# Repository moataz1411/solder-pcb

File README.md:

# solder-pcb

A simple custom shaped PCB designed as a shark keychain with leds.

The goal of the project was to combine electronic circuit with a creative PCB shape to make a cool keychain.

---

## Bill of Materials

| Component | Value | Qty |
|-----------|-------|-----|
| CR2032 Battery Holder | 3V | 1 |
| 5mm LED | Red | 3 |
| Resistor | 470Ω | 3 |
| Push Button | 6mm | 1 |

**Total: 8 components**

---

schematic photo

---

pcb photo

---

3d view

--- 

#my user  : mezoahmed1411

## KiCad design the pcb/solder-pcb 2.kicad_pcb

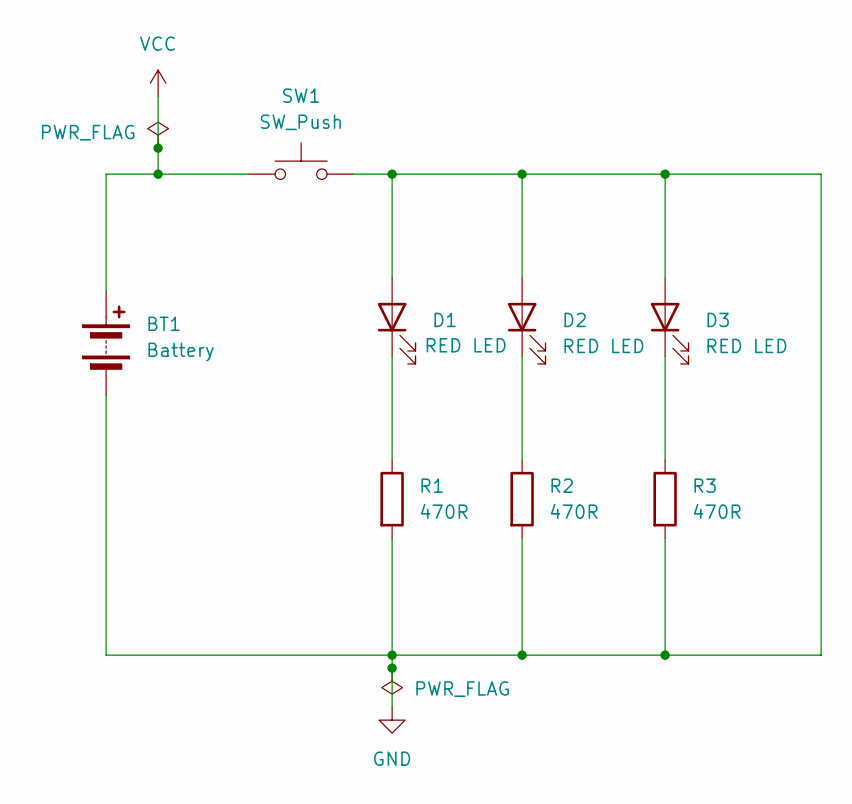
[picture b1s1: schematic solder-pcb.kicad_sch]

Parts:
BT1: Battery; Texas_DRC0010J_ThermalVias
D1, D2, D3: RED LED
R1, R2, R3: 470R
SW1: SW_Push; DIP-24_W7.62mm

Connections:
GND: BT1.2 (-), D1.2 (A), D2.2 (A), D3.2 (A), R1.2, R2.2, R3.2, SW1.2
unnamed: D1.1 (K), R1.1
unnamed: D2.1 (K), R2.1
unnamed: D3.1 (K), R3.1
VCC: BT1.1 (+), SW1.1

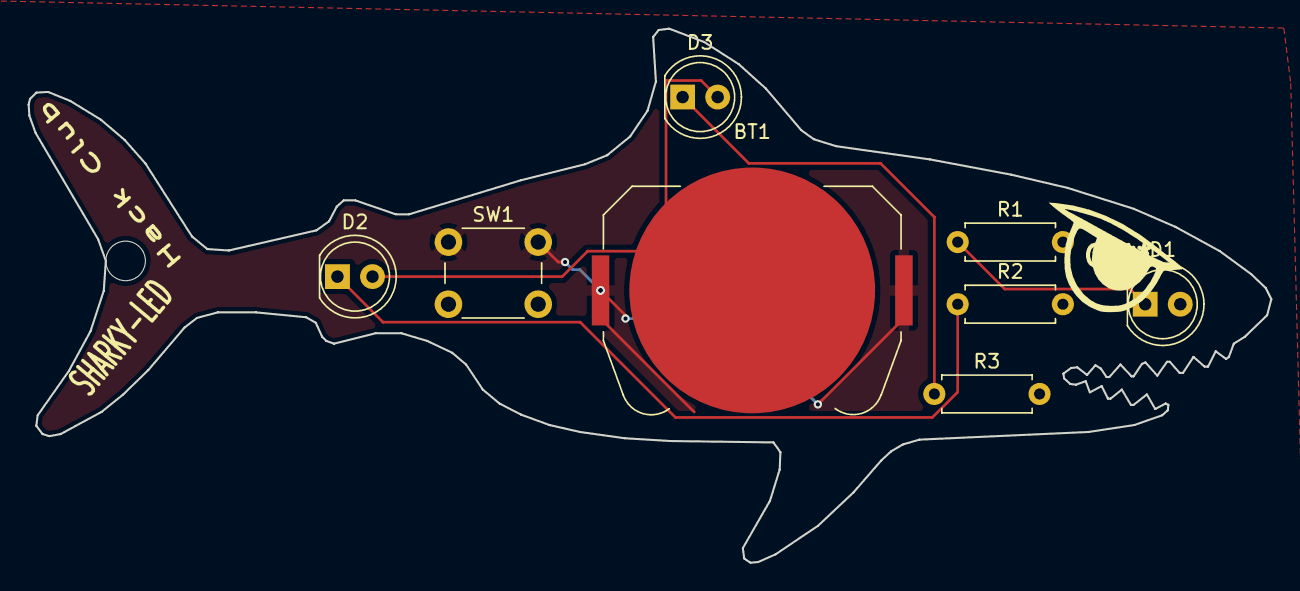
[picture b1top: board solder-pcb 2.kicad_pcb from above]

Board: 2 copper layers, 90.0 x 38.7 mm, 8 parts (0 on the bottom side), 5 nets.
